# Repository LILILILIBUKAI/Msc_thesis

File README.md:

# Msc_thesis
====================
Master thesis digital supplement for Msc. thesis:

	"Bio-inspired inertial sensing by flapping wings"

The Euler-Lagrange model is based on the publication:
 Eberle A, Dickerson B, Reinhall P, and Daniel T. (2015). A new twist on gyroscopic sensing: body rotations lead to torsion in flapping, flexing insect wings. Journal of the Royal Society, Interface. 

The supplement contains 4 main folders: 

	Data
		Comsol_mesh_convergence (4 .CSV files)
		Comsol_simulations (9 .CSV files)
		flapping_data_10_04 (26 .CSV files)
		Matlab_simulations (8 .mat files)
	Matlab
		Aerodynamic_force_estimate
		Euler_Lagrange_simulation
			runsimulations
				flappermodel_rotvect
					createODEfile_rotvect
					funcCa
					PlateODE
					shape2
					shapefunc2
	PCB_design
		amp_shield_v2.3 (.pdf, .brd, .sch)
	Python 
		Compare_quarter_half
		data_analysis_10_04_halfbridge
		data_analysis_10_04_quarterbridge
		eigenfrequency_analysis
		Force_simulation
		Mesh_convergence_analysis
		Simulation_analysis
		thesis_functions

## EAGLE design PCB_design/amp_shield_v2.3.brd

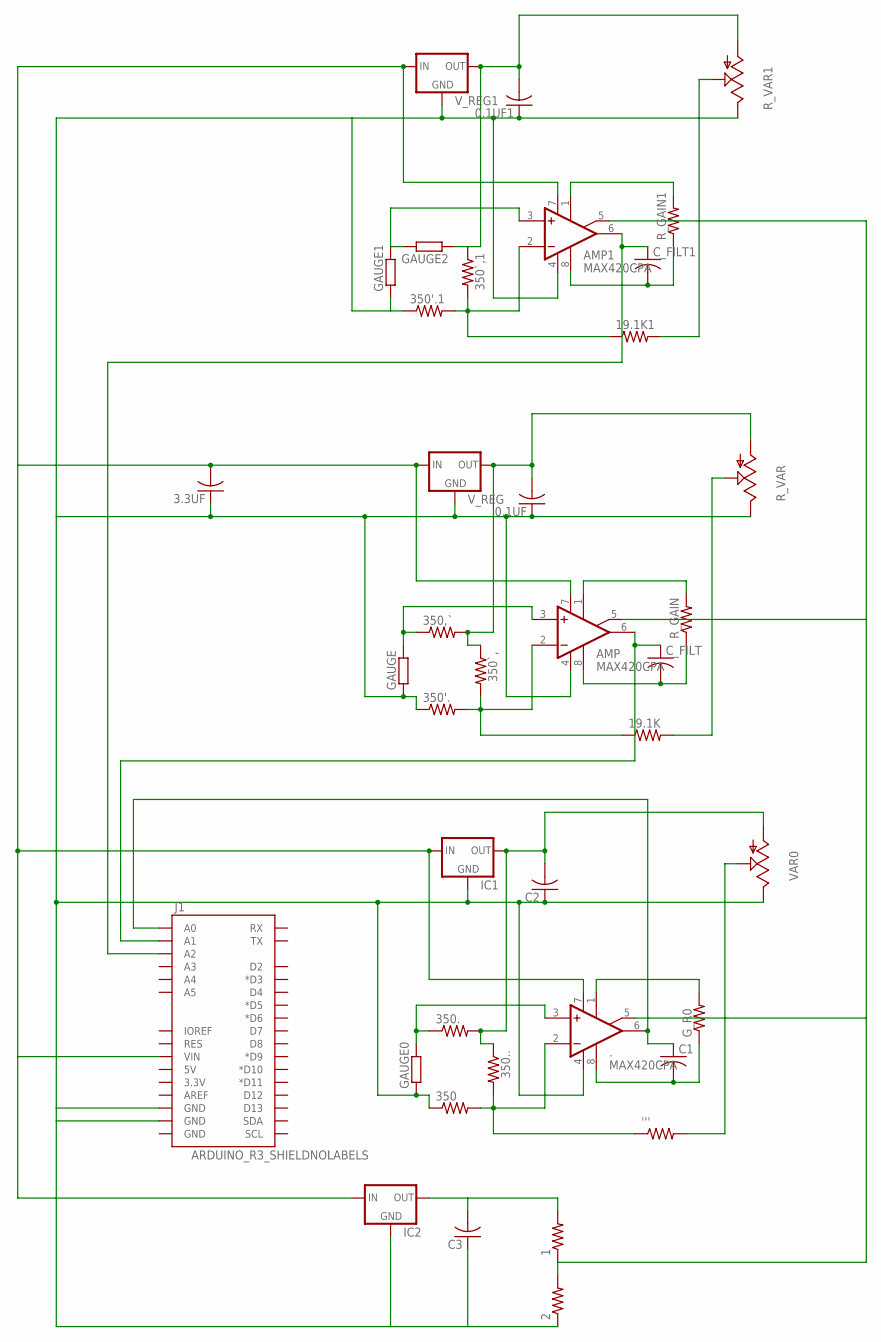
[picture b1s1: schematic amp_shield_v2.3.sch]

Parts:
0.1UF, 0.1UF1, 3.3UF: C-US025-024X044; C025-024X044
1, 2, 19.1K, 19.1K1, 350, 350'., 350'.1, 350,`, 350., 350.., 350`,, 350`,1: R-US_0204/2V; 0204V
''': R-US_0204/2V; 0204V
.: MAX420CPA; DIL08
AMP, AMP1: MAX420CPA; DIL08
C1, C2, C3: C-US025-024X044; C025-024X044
C_FILT, C_FILT1: C-US025-024X044; C025-024X044
GAUGE, GAUGE0, GAUGE1, GAUGE2: R-EU_0204/2V; 0204V
G_R0: R-US_0204/2V; 0204V
IC1, IC2: 78MXXS
J1: ARDUINO_R3_SHIELDNOLABELS; UNO_R3_SHIELD_NOLABELS
R_GAIN, R_GAIN1: R-US_0204/2V; 0204V
R_VAR, R_VAR1: TRIM_US-B64Y; B64Y
VAR0: TRIM_US-B64Y; B64Y
V_REG, V_REG1: 78MXXS

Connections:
0.1UF1: 0.1UF.1, 0.1UF1.1, 2.1, 3.3UF.1, 350.1, 350'..1, 350'.1.1, ..4 (V-), AMP.4 (V-), AMP1.4 (V-), C2.1, C3.1, GAUGE.1, GAUGE0.1, GAUGE1.1, IC1.GND, IC2.GND, J1.GND@1 (GND), J1.GND@2 (GND), R_VAR.E, R_VAR1.E, VAR0.E, V_REG.GND, V_REG1.GND
350.: 350..1, ..3 (+IN), GAUGE0.2
unnamed: 0.1UF.2, 350,`.2, 350`,.1, R_VAR.A, V_REG.OUT
unnamed: '''.2, VAR0.S
unnamed: 350..2, 350...1, C2.2, IC1.OUT, VAR0.A
unnamed: ..1 (CEXTA), G_R0.2
unnamed: ..8 (CEXTB), C1.2, G_R0.1
unnamed: ..6 (OUT), C1.1, J1.A0
unnamed: 350.2, 350...2, '''.1, ..2 (-IN)
unnamed: AMP.8 (CEXTB), C_FILT.2, R_GAIN.1
unnamed: AMP1.8 (CEXTB), C_FILT1.2, R_GAIN1.1
unnamed: AMP.1 (CEXTA), R_GAIN.2
unnamed: AMP.6 (OUT), C_FILT.1, J1.A1
unnamed: 19.1K.1, 350'..2, 350`,.2, AMP.2 (-IN)
unnamed: 350,`.1, AMP.3 (+IN), GAUGE.2
unnamed: 19.1K.2, R_VAR.S
unnamed: AMP1.1 (CEXTA), R_GAIN1.2
unnamed: AMP1.6 (OUT), C_FILT1.1, J1.A2
unnamed: 19.1K1.1, 350'.1.2, 350`,1.2, AMP1.2 (-IN)
unnamed: AMP1.3 (+IN), GAUGE1.2, GAUGE2.2
unnamed: 19.1K1.2, R_VAR1.S
unnamed: 0.1UF1.2, 350`,1.1, GAUGE2.1, R_VAR1.A, V_REG1.OUT
unnamed: 1.2, C3.2, IC2.OUT
unnamed: 1.1, 2.2, ..5 (CRETN), AMP.5 (CRETN), AMP1.5 (CRETN)
V_REG1: 3.3UF.2, ..7 (V+), AMP.7 (V+), AMP1.7 (V+), IC1.IN, IC2.IN, J1.VIN, V_REG.IN, V_REG1.IN

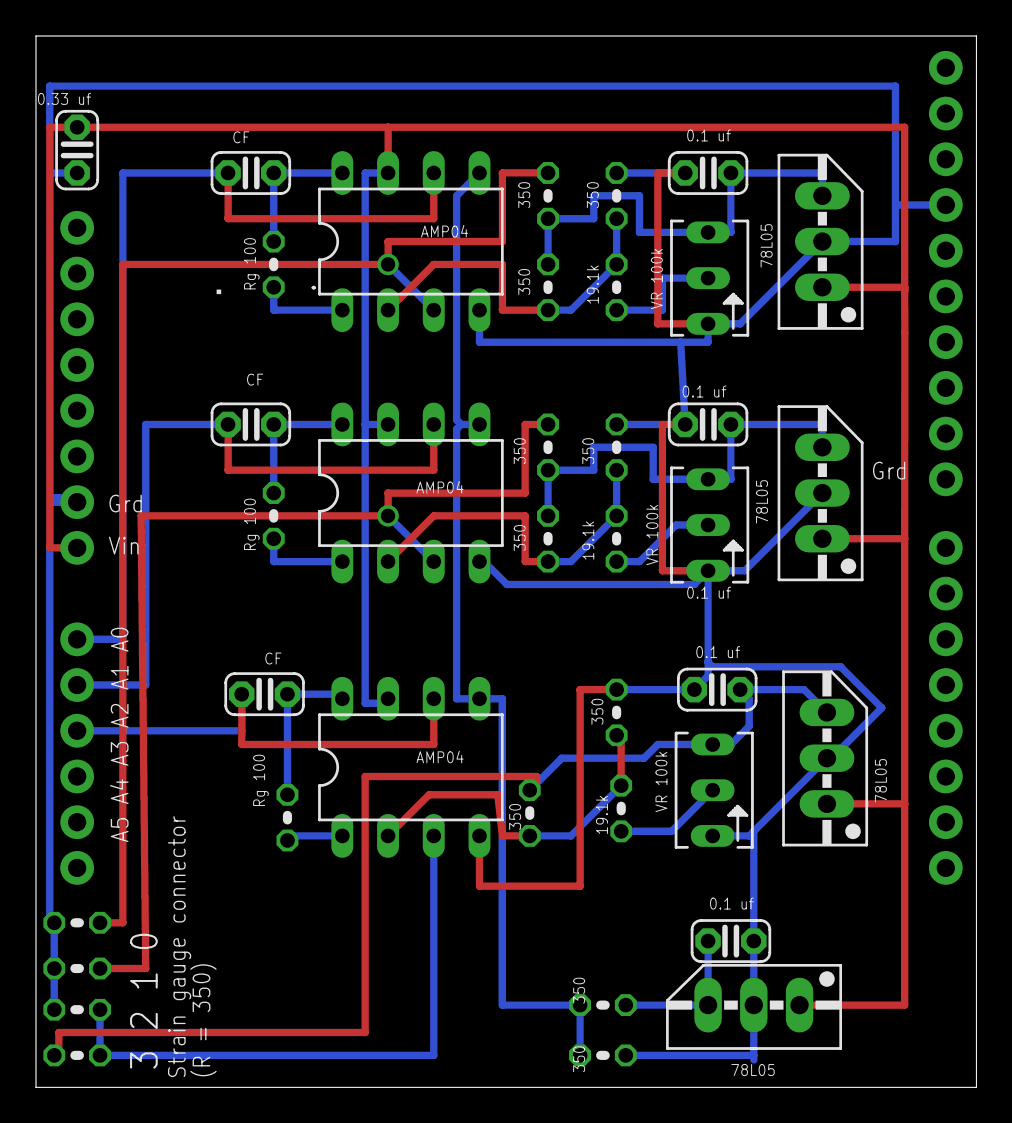
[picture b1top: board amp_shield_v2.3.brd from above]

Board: 2 copper layers, 52.2 x 58.4 mm, 39 parts (0 on the bottom side), 25 nets.

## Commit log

2015-12-01 PCB design
    PCB design for arduino amp shield
2015-12-01 First commit -> Euler-Lagrange model
    Euler-Lagrange model of flapping and rotating flat plate. Taken from
    Eberle et al (2015).
2015-12-01 include startup and change data location
2015-12-01 First commit: python code
    Python code to visualize data
2015-12-01 first comit: more analysis code
2015-12-01 Euler-Lagrange results
2015-12-01 data comits
2015-12-01 Remove unused data and expand on README

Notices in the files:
parts and their libraries:
SparkFun-Boards: Licensing: Creative Commons ShareAlike 4.0 International - https://creativecommons.org/licenses/by-sa/4.0
